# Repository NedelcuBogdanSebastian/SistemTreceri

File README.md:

# Copyright Notice
### Licence
Copyright (C) 2024 Nedelcu Bogdan Sebastian  
This code is free software: you can redistribute it and/or modify it under the following conditions:  
1. The use, distribution, and modification of this file are permitted for any purpose,  
   provided that the following conditions are met:  
2. Any redistribution or modification of this file must retain the original copyright notice,  
   this list of conditions, and the following attribution:  
      **"Original work by Nedelcu Bogdan Sebastian."**   
3. The original author provides no warranty regarding the functionality or fitness of this software  
   for any particular purpose. Use it at your own risk.  
By using this software, you agree to retain the name of the original author in any derivative works or distributions.  
This code is provided as-is, without any express or implied warranties.

# treceri
This is the main project used to acquire leakage currents signals, 
and compute **RMS voltage** and **phase** for each of the six channels.

The acquisition is starting after a **zero-cross detection**, and the length
of data is **2048 samples**.

The limits of the signals are between **2.678 mA** and **100 mA**.

More explanations of the algorithms are in the **main.c** file.

*(Note: The code runs on BluePill (STM32F103CBT6) and the IDE is the CooCox 1.7.8.
        The compiler used is the  gcc-arm-none-eabi-10.3-2021.10-win32.exe.
        Use external 23K256 SRAM memory to store all 6 signals at once!)*

# TestFFTPhaseComputation
This project also runs on the **STM32F103CBT6**.

Here we generate sine waves with phases from 0 to 359 degrees, and add noise to 
each signal and compute the phase angle from FFT.

The BluePill will show on the PC side as a **USB SERIAL** device, and we use this method
to print all values over **SERIAL**, the initial **signal phase** and the **computed phase** 
to further analyze them with Python if needed.

**Termite serial** can be used to receive data.

*(Note: The values are scaled by a factor of 10000 !)*

# treceriTestPhaseComputing

This project is made in **Visual Studio Code**. The compiler used is **tdm64-gcc-10.3.0-2**.

In this example we have the following:

    - we generate signals from 0 degrees to 359 degrees,
      of specific phase and noise, and write the values to files named `sine_wave_x.x.txt`,
      with 1.0 degree step
      
    - we generate the Flattop window and write coeffs to a file `flattop_window.txt`
    
    - we apply the window to the signal real side
    
    - we compute FFT
    
    - we compute the phase from bin 9 which is the nearest frequency from 50 Hz (51.4984130859375 Hz)

    - print computed data and repeat until the phase is >= 360.0 degrees
    
We also have some **Python** scripts we can use to see the signals from the files:

    - the `animate_plot_files.py` loads text files, one after another, 
      and plot the signal and the FFT
      
    - the `plot_sine_wave.py` plot only one file
    
    - the `gen_sig_hanning.py` generate a signal and apply hanning window. 
      Also compute phase.

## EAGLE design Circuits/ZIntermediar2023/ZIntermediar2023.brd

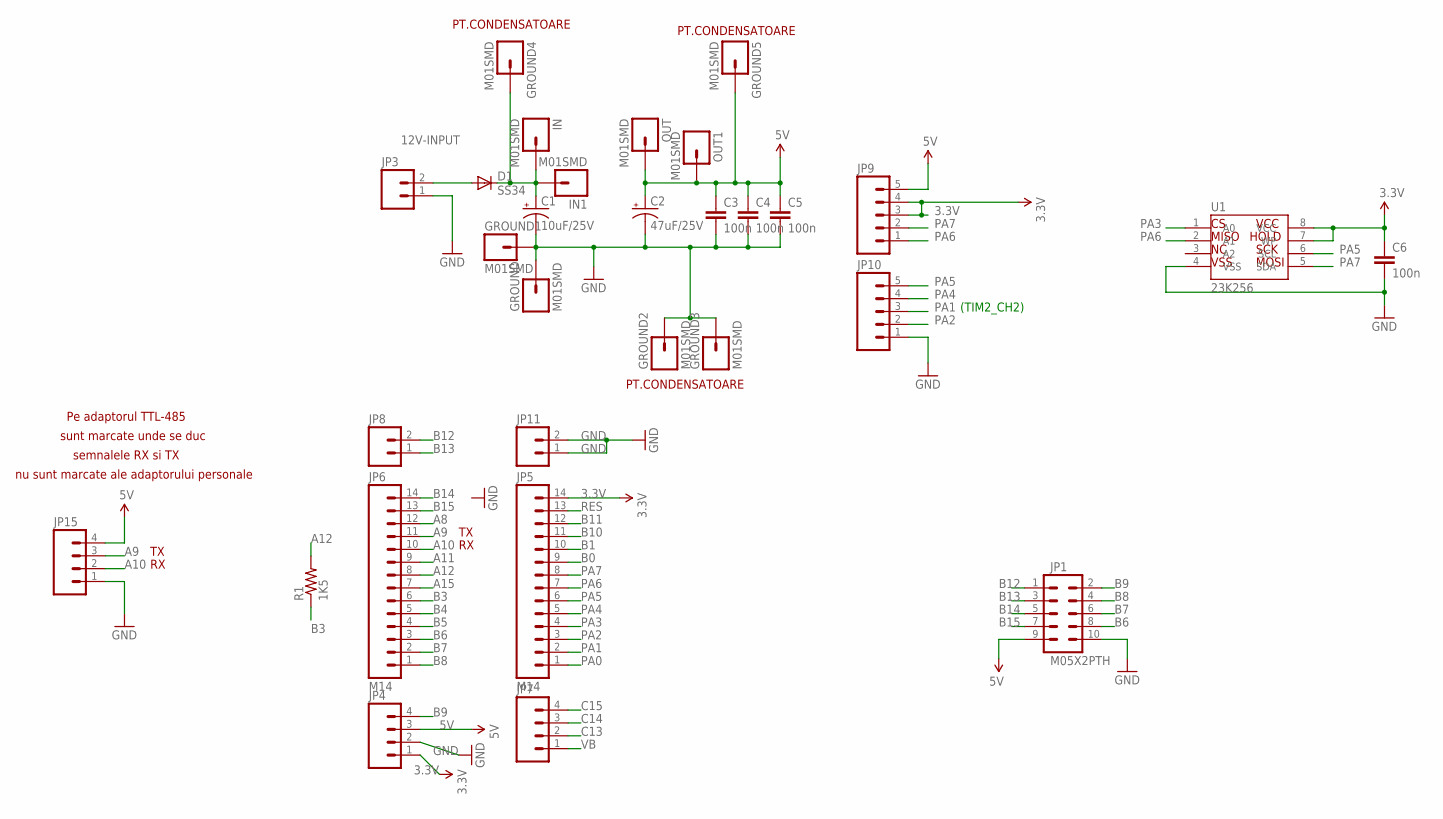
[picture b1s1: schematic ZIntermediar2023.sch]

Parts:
C1: 10uF/25V; PANASONIC_E
C2: 47uF/25V; PANASONIC_E
C3, C4, C5, C6: 100n; 1206
D1: SS34; SMC
GROUND, GROUND1, GROUND2, GROUND3, GROUND4, GROUND5: M01SMD; LUXEON-PAD
IN, IN1: M01SMD; LUXEON-PAD
JP1: M05X2PTH; AVR_ICSP
JP3: M025MM; SCREWTERMINAL-5MM-2
JP4, JP7: M04PTH; 1X04
JP5, JP6: M14; 1X14
JP8, JP11: M02PTH; 1X02
JP9, JP10: M05PTH_LONGPADS; 1X05_LONGPADS
JP15: M04LONGPADS; 1X04_LONGPADS
OUT, OUT1: M01SMD; LUXEON-PAD
R1: 1K5; 1206
U1: 23K256; SO08

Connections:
3.3V: C6.1, JP4.1, JP5.14, JP9.3, JP9.4, U1.7 (WP), U1.8 (VCC)
5V: C2.+, C3.1, C4.1, C5.1, GROUND5.P$1, JP1.9, JP4.3, JP9.5, JP15.4, OUT.P$1, OUT1.P$1
12V-INPUT: C1.+, D1.C, GROUND4.P$1, IN.P$1, IN1.P$1
A8: JP6.12
A9: JP6.11, JP15.3
A10: JP6.10, JP15.2
A11: JP6.9
A12: JP6.8, R1.2
A15: JP6.7
B0: JP5.9
B1: JP5.10
B3: JP6.6, R1.1
B4: JP6.5
B5: JP6.4
B6: JP1.8, JP6.3
B7: JP1.6, JP6.2
B8: JP1.4, JP6.1
B9: JP1.2, JP4.4
B10: JP5.11
B11: JP5.12
B12: JP1.1, JP8.2
B13: JP1.3, JP8.1
B14: JP1.5, JP6.14
B15: JP1.7, JP6.13
C13: JP7.2
C14: JP7.3
C15: JP7.4
GND: C1.-, C2.-, C3.2, C4.2, C5.2, C6.2, GROUND.P$1, GROUND1.P$1, GROUND2.P$1, GROUND3.P$1, JP1.10, JP3.1, JP4.2, JP10.1, JP11.1, JP11.2, JP15.1, U1.4 (VSS)
unnamed: D1.A, JP3.2
PA0: JP5.1
PA1: JP5.2, JP10.3
PA2: JP5.3, JP10.2
PA3: JP5.4, U1.1 (A0)
PA4: JP5.5, JP10.4
PA5: JP5.6, JP10.5, U1.6 (SCL)
PA6: JP5.7, JP9.1, U1.2 (A1)
PA7: JP5.8, JP9.2, U1.5 (SDA)
RES: JP5.13
VB: JP7.1

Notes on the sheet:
(TIM2_CH2)
MISO
VSS
VCC
HOLD
SCK
MOSI
PT.CONDENSATOARE
Pe adaptorul TTL-485
sunt marcate unde se duc
semnalele RX si TX
nu sunt marcate ale adaptorului personale

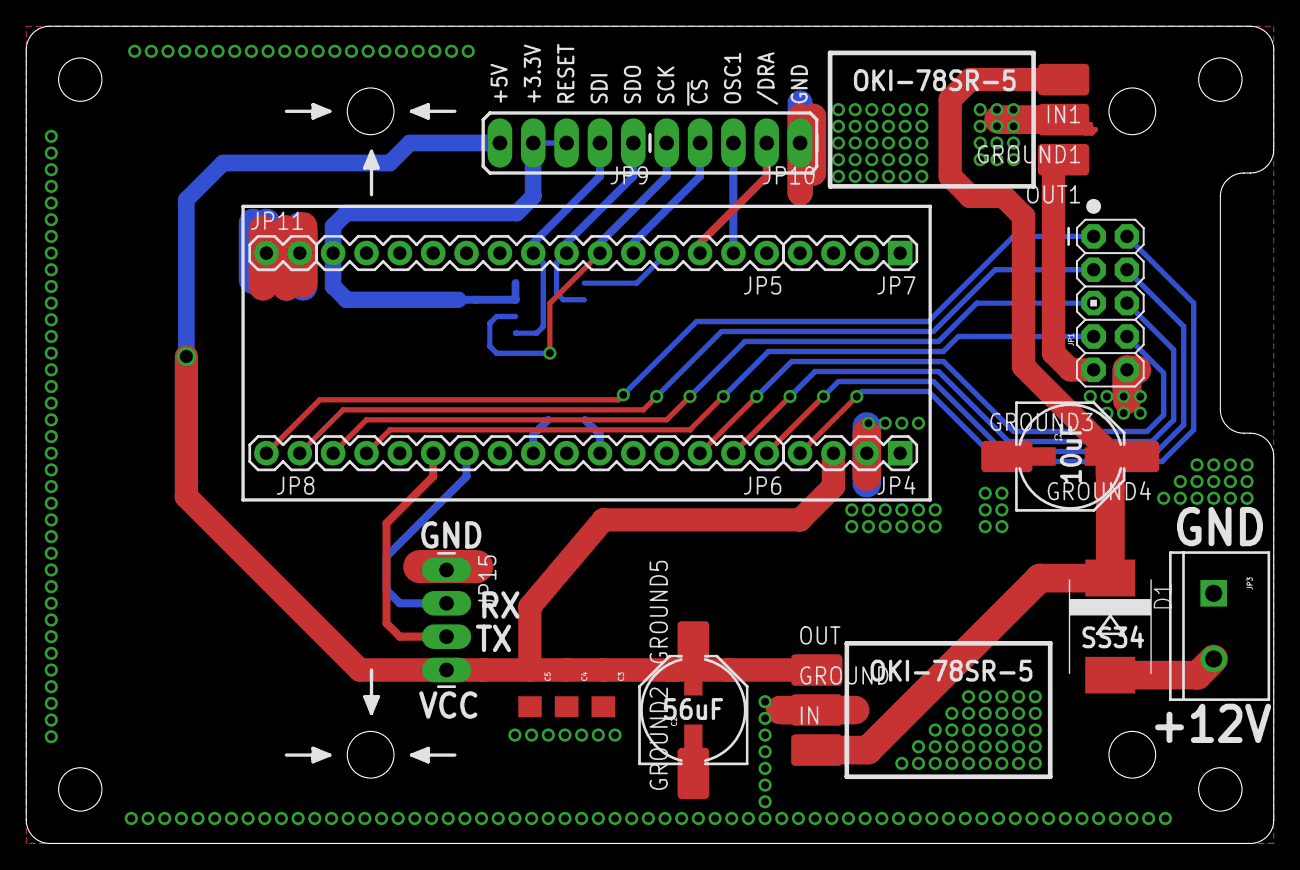
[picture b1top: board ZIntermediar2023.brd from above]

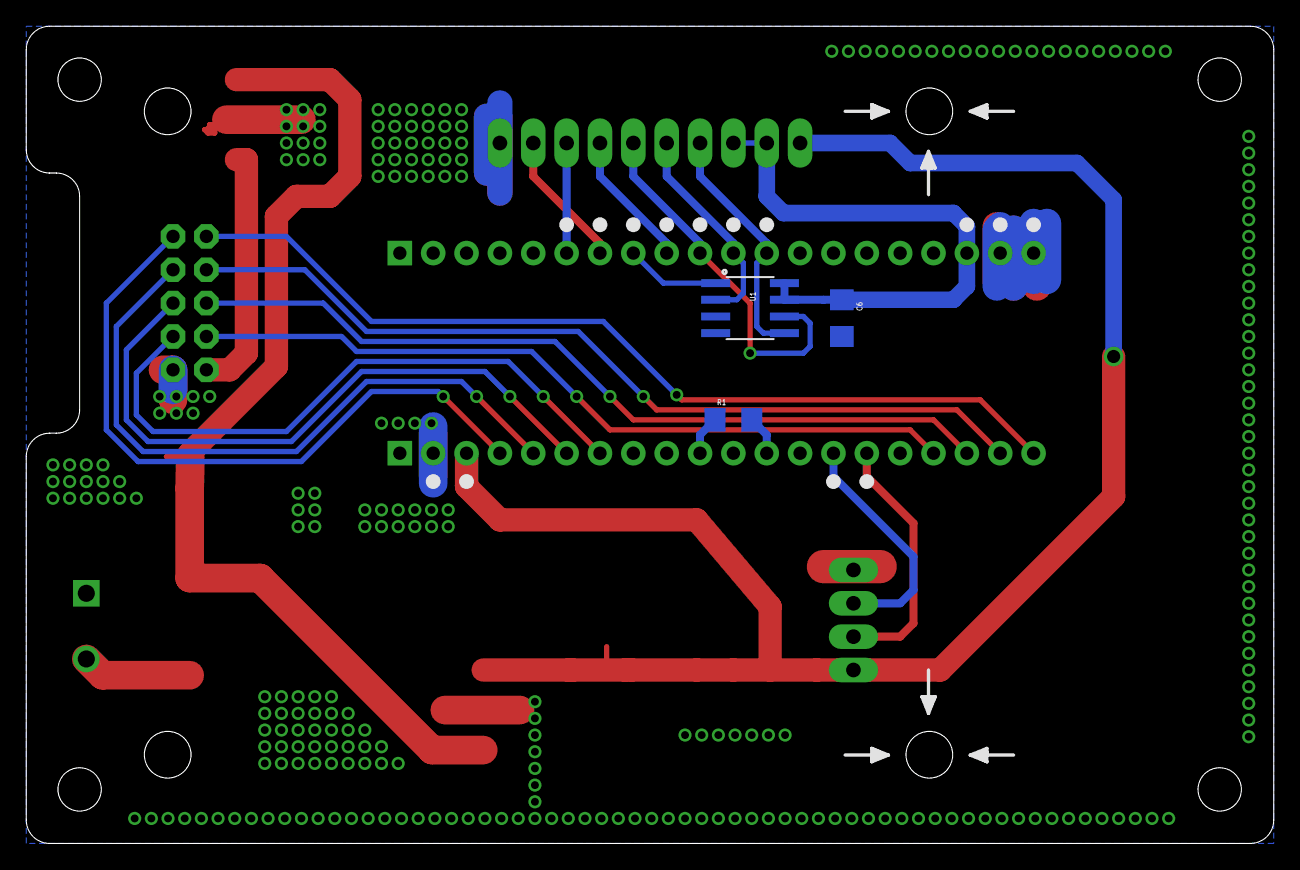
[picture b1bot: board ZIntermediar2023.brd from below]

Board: 2 copper layers, 95.0 x 62.2 mm, 34 parts (3 on the bottom side), 24 nets.

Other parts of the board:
STANDOFF1, STANDOFF6, STANDOFF10, STANDOFF12: STAND-OFF

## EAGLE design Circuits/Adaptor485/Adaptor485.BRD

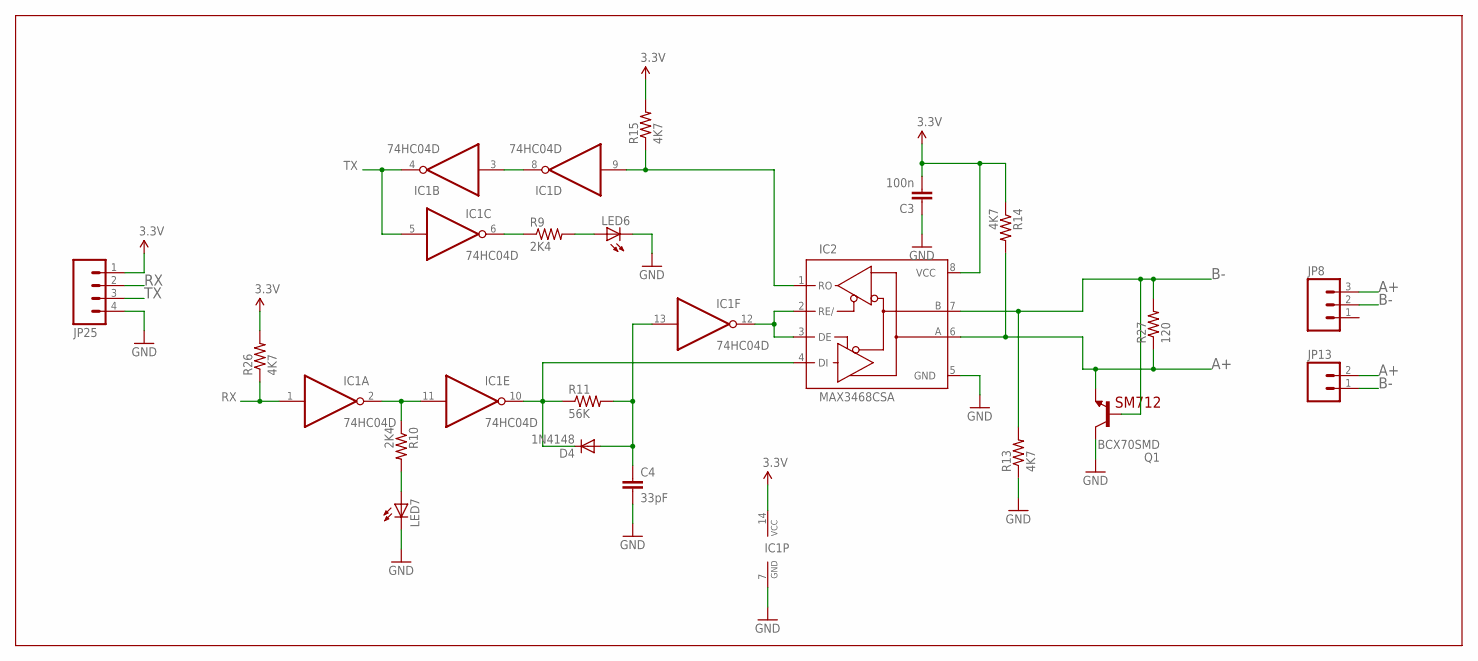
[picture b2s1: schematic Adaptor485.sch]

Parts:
C3: 100n; 0805
C4: 33pF; 0805
D4: 1N4148; MINIMELF
IC1: 74HC04D; SO14
IC2: MAX3468CSA; SO08
JP8: M03-SCREW-5MM; SCREWTERMINAL-5MM-3
JP13: M025MM; SCREWTERMINAL-5MM-2
JP25: M04PTH; 1X04
LED6, LED7: LEDCHIP-LED0805; CHIP-LED0805
Q1: BCX70SMD; SOT23
R9, R10: 2K4; 0805
R11: 56K; 0805
R13, R14, R15, R26: 4K7; 0805
R27: 120; 0805

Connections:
3.3V: C3.2, IC1.14 (VCC), IC2.8 (VCC), JP25.1, R14.1, R15.2, R26.2
A+: IC2.6 (A), JP8.3, JP13.2, Q1.2 (E), R14.2, R27.1
B-: IC2.7 (B), JP8.2, JP13.1, Q1.1 (B), R13.2, R27.2
GND: C3.1, C4.2, IC1.7 (GND), IC2.5 (GND), JP25.4, LED6.C, LED7.C, Q1.3 (C), R13.1
unnamed: LED7.A, R10.2
unnamed: LED6.A, R9.2
unnamed: IC1.2 (O), IC1.11 (I), R10.1
unnamed: IC1.9 (I), IC2.1 (RO), R15.1
unnamed: IC1.3 (I), IC1.8 (O)
unnamed: C4.1, D4.A, IC1.13 (I), R11.2
unnamed: IC1.6 (O), R9.1
unnamed: D4.C, IC1.10 (O), IC2.4 (DI), R11.1
unnamed: IC1.12 (O), IC2.2 (RE/), IC2.3 (DE)
RX: IC1.1 (I), JP25.2, R26.1
TX: IC1.4 (O), IC1.5 (I), JP25.3

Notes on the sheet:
SM712

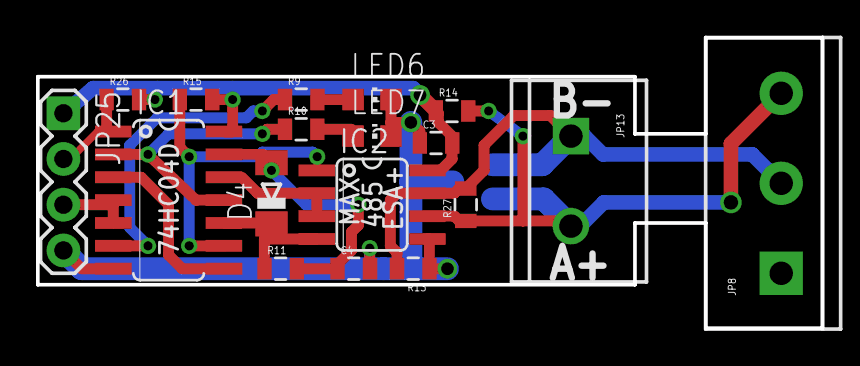
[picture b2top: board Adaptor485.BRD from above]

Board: 2 copper layers, 43.6 x 16.1 mm, 19 parts (1 on the bottom side), 15 nets.

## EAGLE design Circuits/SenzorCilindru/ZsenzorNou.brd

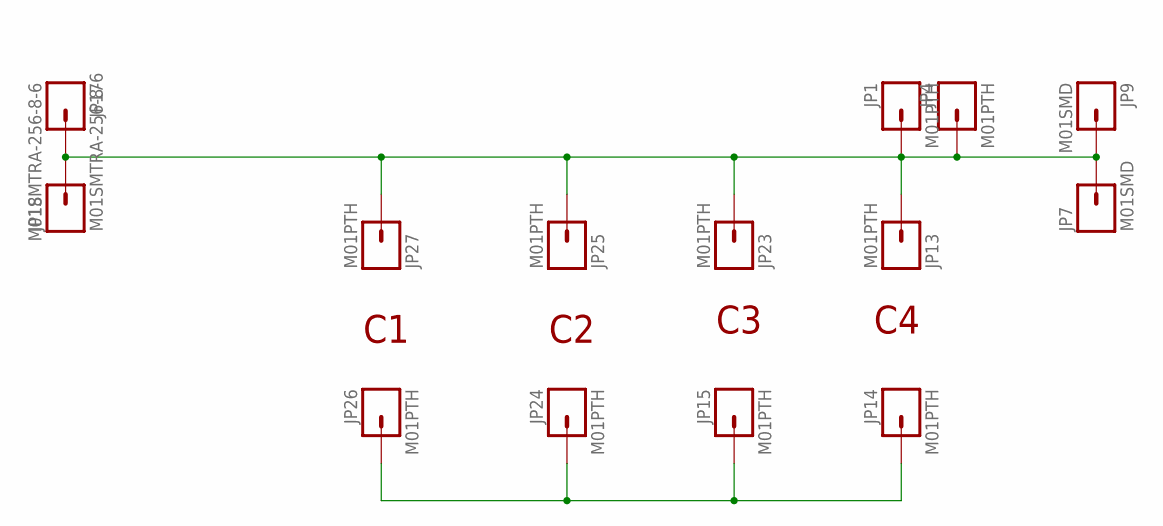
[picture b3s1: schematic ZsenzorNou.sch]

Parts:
JP1, JP4, JP13, JP14, JP15, JP23, JP24, JP25, JP26, JP27: M01PTH; 1X01
JP7, JP9: M01SMD; LUXEON-PAD
JP17, JP18: M01SMTRA-256-8-6; SMTRA-256-8-6

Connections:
GND: JP14.1, JP15.1, JP24.1, JP26.1
unnamed: JP1.1, JP4.1, JP7.P$1, JP9.P$1, JP13.1, JP17.P$1, JP18.P$1, JP23.1, JP25.1, JP27.1

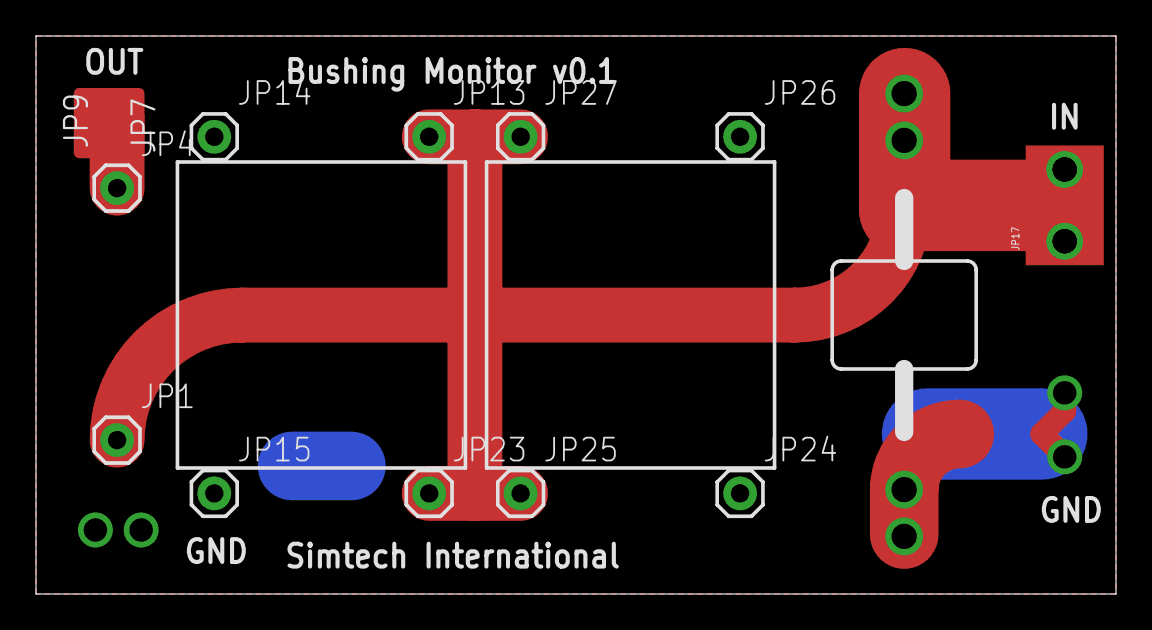
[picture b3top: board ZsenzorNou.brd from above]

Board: 2 copper layers, 60.0 x 31.0 mm, 14 parts (1 on the bottom side), 2 nets.

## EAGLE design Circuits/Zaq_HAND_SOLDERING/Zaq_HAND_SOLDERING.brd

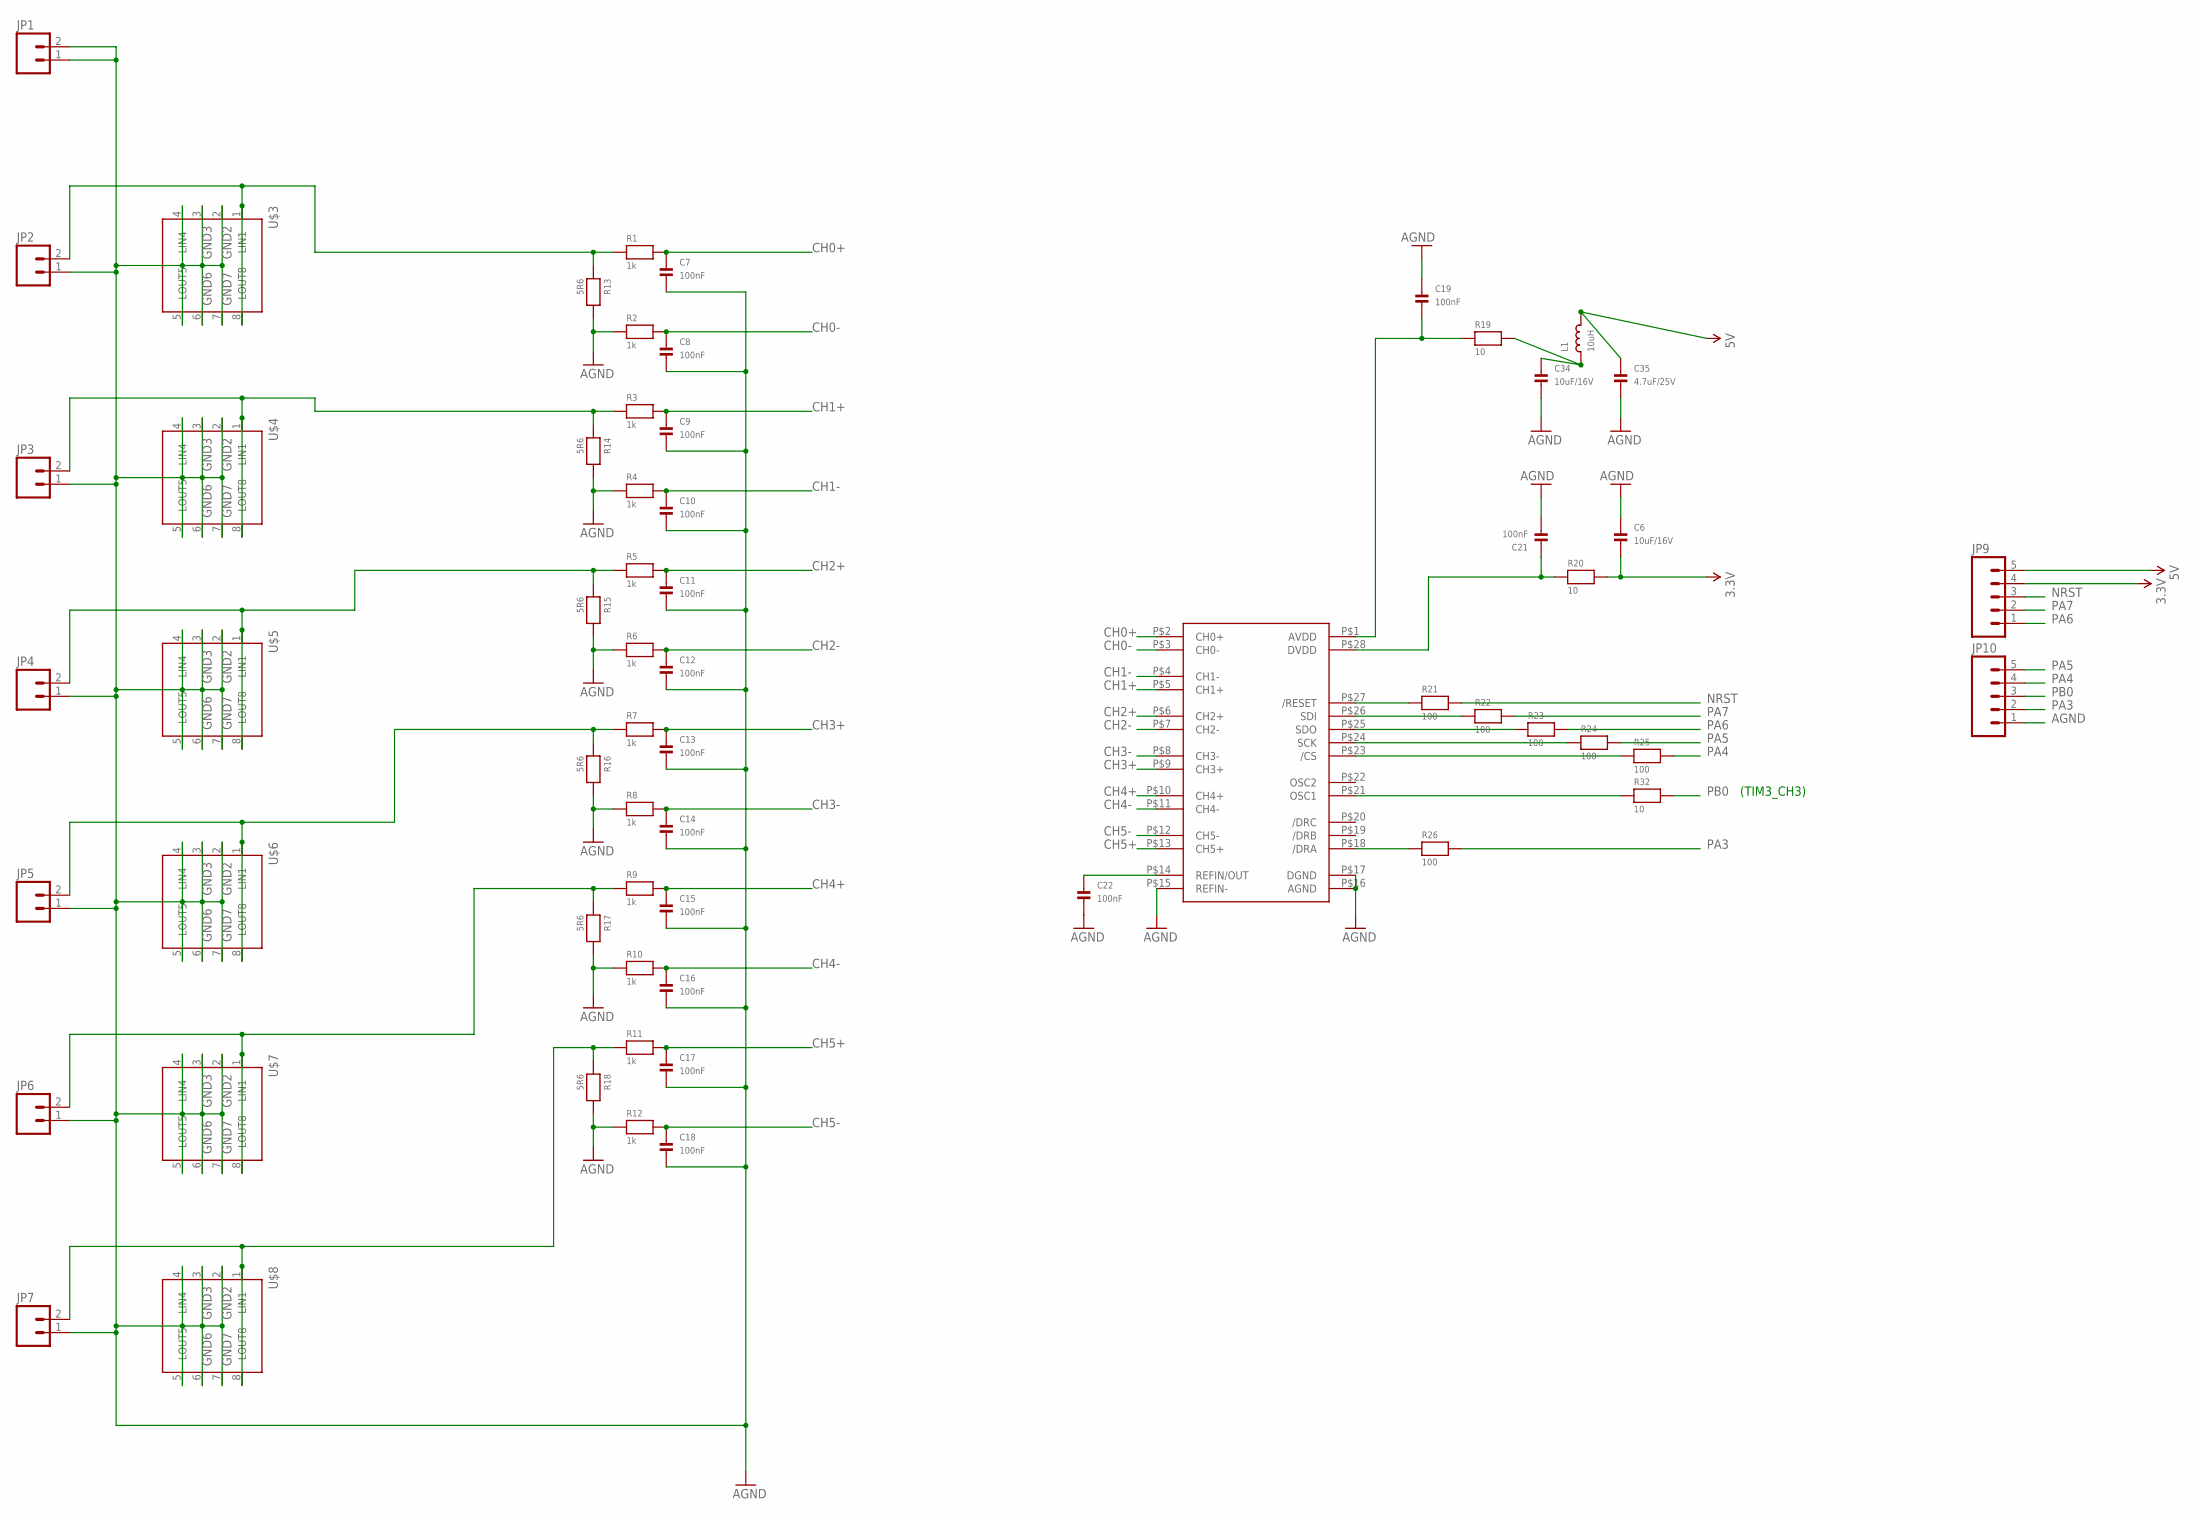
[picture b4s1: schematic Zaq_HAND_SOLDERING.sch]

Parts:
.: MCP3903; SSOP-28
C6, C34: 10uF/16V; _0805MP
C7, C8, C9, C10, C11, C12, C13, C14, C15, C16, C17, C18, C19, C21, C22: 100nF; _0805MP
C35: 4.7uF/25V; _0805MP
JP1, JP2, JP3, JP4, JP5, JP6, JP7: M025MM; SCREWTERMINAL-5MM-2
JP9, JP10: M05PTH_LONGPADS; 1X05_LONGPADS
L1: 10uH; _0805MP
R1, R2, R3, R4, R5, R6, R7, R8, R9, R10, R11, R12: 1k; _0805MP
R13, R14, R15, R16, R17, R18: 5R6; 1206
R19, R20, R32: 10; _0805MP
R21, R22, R23, R24, R25, R26: 100; _0805MP
U$3, U$4, U$5, U$6, U$7, U$8: LC03_3V3; SO8

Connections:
3.3V: C6.2, JP9.4, R20.2
5V: C35.1, JP9.5, L1.2
AGND: ..P$15 (REFIN-), ..P$16 (AGND), ..P$17 (DGND), C6.1, C7.2, C8.2, C9.2, C10.2, C11.2, C12.2, C13.2, C14.2, C15.2, C16.2, C17.2, C18.2, C19.1, C21.2, C22.2, C34.2, C35.2, JP1.1, JP1.2, JP2.1, JP3.1, JP4.1, JP5.1, JP6.1, JP7.1, JP10.1, R2.1, R4.1, R6.1, R8.1, R10.1, R12.1, R13.2, R14.2, R15.2, R16.2, R17.2, R18.2, U$3.2 (GND_2), U$3.3 (GND_3), U$3.4 (LIN4), U$3.5 (LOUT5), U$3.6 (GND_6), U$3.7 (GND_7), U$4.2 (GND_2), U$4.3 (GND_3), U$4.4 (LIN4), U$4.5 (LOUT5), U$4.6 (GND_6), U$4.7 (GND_7), U$5.2 (GND_2), U$5.3 (GND_3), U$5.4 (LIN4), U$5.5 (LOUT5), U$5.6 (GND_6), U$5.7 (GND_7), U$6.2 (GND_2), U$6.3 (GND_3), U$6.4 (LIN4), U$6.5 (LOUT5), U$6.6 (GND_6), U$6.7 (GND_7), U$7.2 (GND_2), U$7.3 (GND_3), U$7.4 (LIN4), U$7.5 (LOUT5), U$7.6 (GND_6), U$7.7 (GND_7), U$8.2 (GND_2), U$8.3 (GND_3), U$8.4 (LIN4), U$8.5 (LOUT5), U$8.6 (GND_6), U$8.7 (GND_7)
CH0+: ..P$2 (CH0+), C7.1, R1.2
CH0-: ..P$3 (CH0-), C8.1, R2.2
CH1+: ..P$5 (CH1+), C9.1, R3.2
CH1-: ..P$4 (CH1-), C10.1, R4.2
CH2+: ..P$6 (CH2+), C11.1, R5.2
CH2-: ..P$7 (CH2-), C12.1, R6.2
CH3+: ..P$9 (CH3+), C13.1, R7.2
CH3-: ..P$8 (CH3-), C14.1, R8.2
CH4+: ..P$10 (CH4+), C15.1, R9.2
CH4-: ..P$11 (CH4-), C16.1, R10.2
CH5+: ..P$13 (CH5+), C17.1, R11.2
CH5-: ..P$12 (CH5-), C18.1, R12.2
unnamed: ..P$21 (OSC1), R32.1
unnamed: ..P$1 (AVDD), C19.2, R19.1
unnamed: ..P$14 (REFIN/OUT), C22.1
unnamed: ..P$28 (DVDD), C21.1, R20.1
unnamed: ..P$27 (/RESET), R21.1
unnamed: ..P$26 (SDI), R22.1
unnamed: ..P$25 (SDO), R23.1
unnamed: ..P$24 (SCK), R24.1
unnamed: ..P$23 (/CS), R25.1
unnamed: ..P$18 (/DRA), R26.1
unnamed: C34.1, L1.1, R19.2
unnamed: JP7.2, R11.1, R18.1, U$8.1 (LIN1), U$8.8 (LOUT8)
unnamed: JP6.2, R9.1, R17.1, U$7.1 (LIN1), U$7.8 (LOUT8)
unnamed: JP5.2, R7.1, R16.1, U$6.1 (LIN1), U$6.8 (LOUT8)
unnamed: JP4.2, R5.1, R15.1, U$5.1 (LIN1), U$5.8 (LOUT8)
unnamed: JP3.2, R3.1, R14.1, U$4.1 (LIN1), U$4.8 (LOUT8)
unnamed: JP2.2, R1.1, R13.1, U$3.1 (LIN1), U$3.8 (LOUT8)
NRST: JP9.3, R21.2
PA3: JP10.2, R26.2
PA4: JP10.4, R25.2
PA5: JP10.5, R24.2
PA6: JP9.1, R23.2
PA7: JP9.2, R22.2
PB0: JP10.3, R32.2

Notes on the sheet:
(TIM3_CH3)

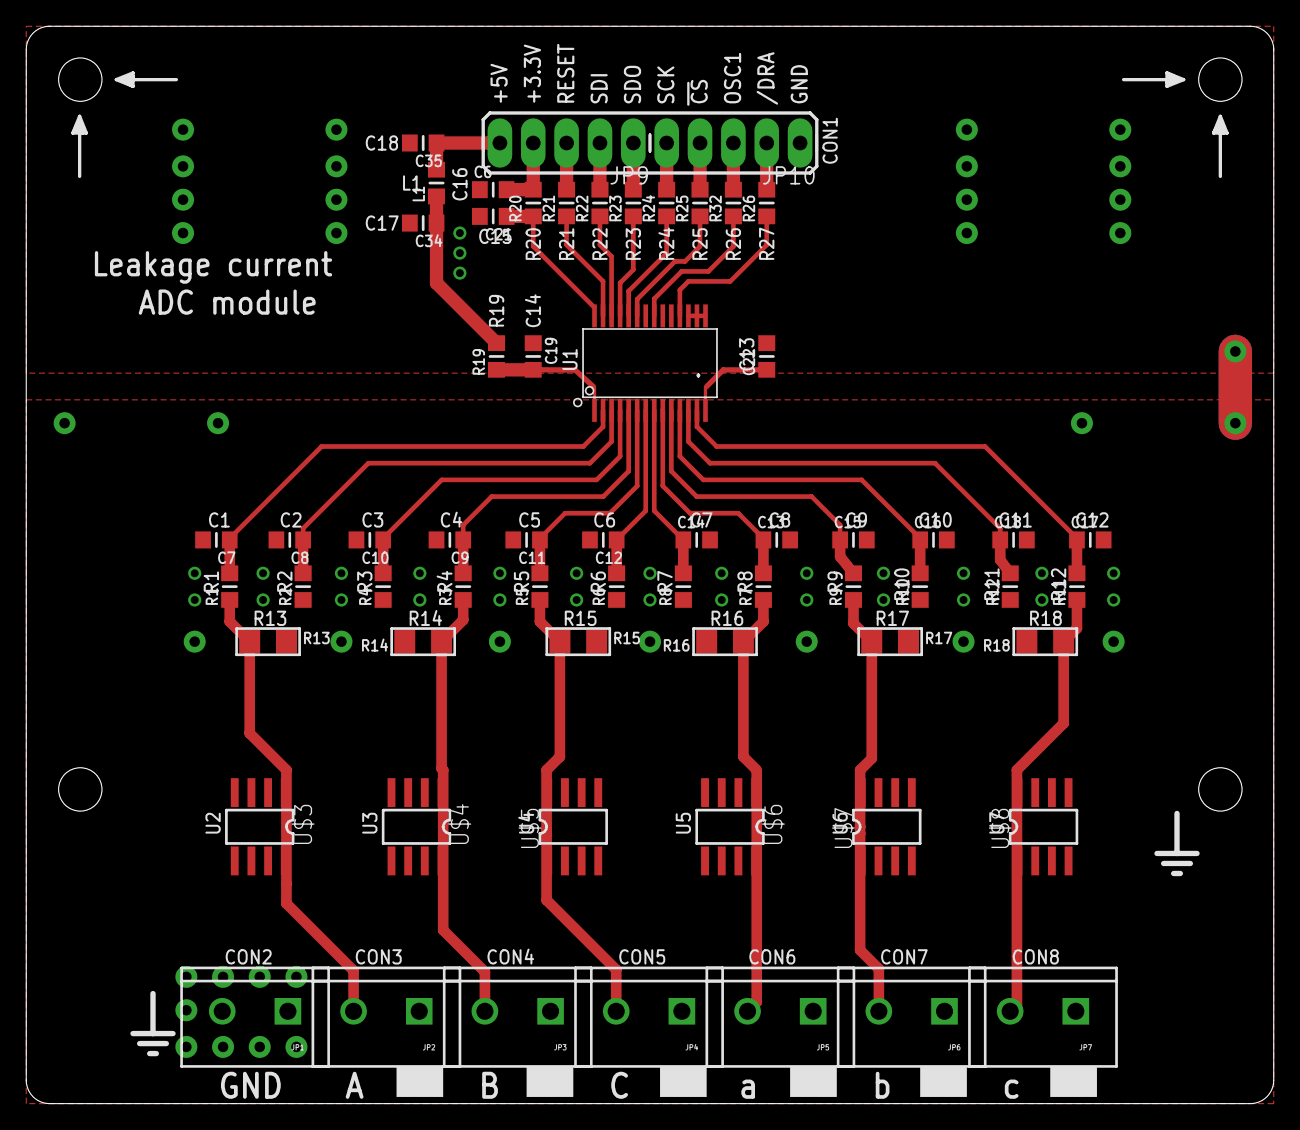
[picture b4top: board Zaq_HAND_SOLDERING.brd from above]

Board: 2 copper layers, 95.0 x 82.0 mm, 66 parts (0 on the bottom side), 39 nets.

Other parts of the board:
STANDOFF1, STANDOFF6, STANDOFF10, STANDOFF12: STAND-OFF

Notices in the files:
parts and their libraries:
SparkFun-Connectors: Licensing: CC v3.0 Share-Alike You are welcome to use this library for commercial purposes.
SparkFun-Passives: Licensing: Creative Commons ShareAlike 4.0 International - https://creativecommons.org/licenses/by-sa/4.0
